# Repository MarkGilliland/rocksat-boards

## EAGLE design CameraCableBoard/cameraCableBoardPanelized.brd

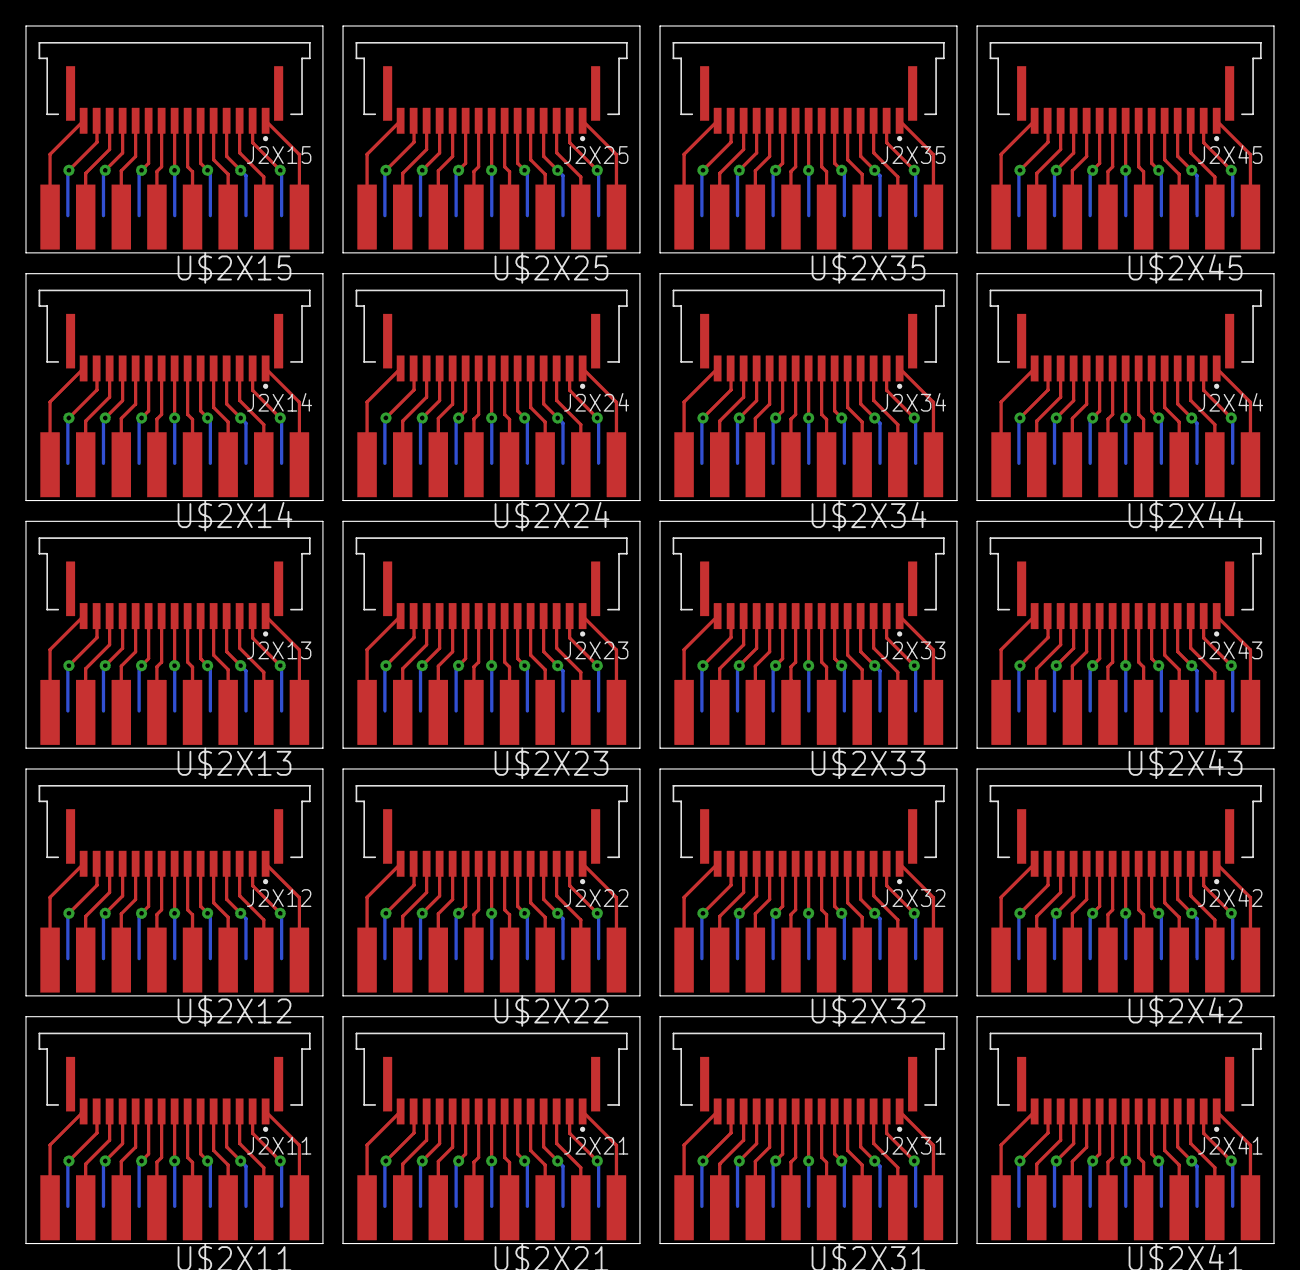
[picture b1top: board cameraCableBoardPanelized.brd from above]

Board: 2 copper layers, 96.0 x 93.7 mm, 40 parts (0 on the bottom side), 300 nets.

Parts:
J2X11, J2X12, J2X13, J2X14, J2X15, J2X21, J2X22, J2X23, J2X24, J2X25, J2X31, J2X32, J2X33, J2X34, J2X35, J2X41, J2X42, J2X43, J2X44, J2X45: AMPHENOL_SFW15R-1STE1LF
U$2X11, U$2X12, U$2X13, U$2X14, U$2X15, U$2X21, U$2X22, U$2X23, U$2X24, U$2X25, U$2X31, U$2X32, U$2X33, U$2X34, U$2X35, U$2X41, U$2X42, U$2X43, U$2X44, U$2X45: DB15-BOARD-EDGE

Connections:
CAM1X11: J2X11.1, U$2X11.P8
CAM1X12: J2X12.1, U$2X12.P8
CAM1X13: J2X13.1, U$2X13.P8
CAM1X14: J2X14.1, U$2X14.P8
CAM1X15: J2X15.1, U$2X15.P8
CAM1X21: J2X21.1, U$2X21.P8
CAM1X22: J2X22.1, U$2X22.P8
CAM1X23: J2X23.1, U$2X23.P8
CAM1X24: J2X24.1, U$2X24.P8
CAM1X25: J2X25.1, U$2X25.P8
CAM1X31: J2X31.1, U$2X31.P8
CAM1X32: J2X32.1, U$2X32.P8
CAM1X33: J2X33.1, U$2X33.P8
CAM1X34: J2X34.1, U$2X34.P8
CAM1X35: J2X35.1, U$2X35.P8
CAM1X41: J2X41.1, U$2X41.P8
CAM1X42: J2X42.1, U$2X42.P8
CAM1X43: J2X43.1, U$2X43.P8
CAM1X44: J2X44.1, U$2X44.P8
CAM1X45: J2X45.1, U$2X45.P8
CAM2X11: J2X11.2, U$2X11.P15
CAM2X12: J2X12.2, U$2X12.P15
CAM2X13: J2X13.2, U$2X13.P15
CAM2X14: J2X14.2, U$2X14.P15
CAM2X15: J2X15.2, U$2X15.P15
CAM2X21: J2X21.2, U$2X21.P15
CAM2X22: J2X22.2, U$2X22.P15
CAM2X23: J2X23.2, U$2X23.P15
CAM2X24: J2X24.2, U$2X24.P15
CAM2X25: J2X25.2, U$2X25.P15
CAM2X31: J2X31.2, U$2X31.P15
CAM2X32: J2X32.2, U$2X32.P15
CAM2X33: J2X33.2, U$2X33.P15
CAM2X34: J2X34.2, U$2X34.P15
CAM2X35: J2X35.2, U$2X35.P15
CAM2X41: J2X41.2, U$2X41.P15
CAM2X42: J2X42.2, U$2X42.P15
CAM2X43: J2X43.2, U$2X43.P15
CAM2X44: J2X44.2, U$2X44.P15
CAM2X45: J2X45.2, U$2X45.P15
CAM3X11: J2X11.3, U$2X11.P7
CAM3X12: J2X12.3, U$2X12.P7
CAM3X13: J2X13.3, U$2X13.P7
CAM3X14: J2X14.3, U$2X14.P7
CAM3X15: J2X15.3, U$2X15.P7
CAM3X21: J2X21.3, U$2X21.P7
CAM3X22: J2X22.3, U$2X22.P7
CAM3X23: J2X23.3, U$2X23.P7
CAM3X24: J2X24.3, U$2X24.P7
CAM3X25: J2X25.3, U$2X25.P7
CAM3X31: J2X31.3, U$2X31.P7
CAM3X32: J2X32.3, U$2X32.P7
CAM3X33: J2X33.3, U$2X33.P7
CAM3X34: J2X34.3, U$2X34.P7
CAM3X35: J2X35.3, U$2X35.P7
CAM3X41: J2X41.3, U$2X41.P7
CAM3X42: J2X42.3, U$2X42.P7
CAM3X43: J2X43.3, U$2X43.P7
CAM3X44: J2X44.3, U$2X44.P7
CAM3X45: J2X45.3, U$2X45.P7
CAM4X11: J2X11.4, U$2X11.P14
CAM4X12: J2X12.4, U$2X12.P14
CAM4X13: J2X13.4, U$2X13.P14
CAM4X14: J2X14.4, U$2X14.P14
CAM4X15: J2X15.4, U$2X15.P14
CAM4X21: J2X21.4, U$2X21.P14
CAM4X22: J2X22.4, U$2X22.P14
CAM4X23: J2X23.4, U$2X23.P14
CAM4X24: J2X24.4, U$2X24.P14
CAM4X25: J2X25.4, U$2X25.P14
CAM4X31: J2X31.4, U$2X31.P14
CAM4X32: J2X32.4, U$2X32.P14
CAM4X33: J2X33.4, U$2X33.P14
CAM4X34: J2X34.4, U$2X34.P14
CAM4X35: J2X35.4, U$2X35.P14
CAM4X41: J2X41.4, U$2X41.P14
CAM4X42: J2X42.4, U$2X42.P14
CAM4X43: J2X43.4, U$2X43.P14
CAM4X44: J2X44.4, U$2X44.P14
CAM4X45: J2X45.4, U$2X45.P14
CAM5X11: J2X11.5, U$2X11.P6
CAM5X12: J2X12.5, U$2X12.P6
CAM5X13: J2X13.5, U$2X13.P6
CAM5X14: J2X14.5, U$2X14.P6
CAM5X15: J2X15.5, U$2X15.P6
CAM5X21: J2X21.5, U$2X21.P6
CAM5X22: J2X22.5, U$2X22.P6
CAM5X23: J2X23.5, U$2X23.P6
CAM5X24: J2X24.5, U$2X24.P6
CAM5X25: J2X25.5, U$2X25.P6
CAM5X31: J2X31.5, U$2X31.P6
CAM5X32: J2X32.5, U$2X32.P6
CAM5X33: J2X33.5, U$2X33.P6
CAM5X34: J2X34.5, U$2X34.P6
CAM5X35: J2X35.5, U$2X35.P6
CAM5X41: J2X41.5, U$2X41.P6
CAM5X42: J2X42.5, U$2X42.P6
CAM5X43: J2X43.5, U$2X43.P6
CAM5X44: J2X44.5, U$2X44.P6
CAM5X45: J2X45.5, U$2X45.P6
CAM6X11: J2X11.6, U$2X11.P13
CAM6X12: J2X12.6, U$2X12.P13
CAM6X13: J2X13.6, U$2X13.P13
CAM6X14: J2X14.6, U$2X14.P13
CAM6X15: J2X15.6, U$2X15.P13
CAM6X21: J2X21.6, U$2X21.P13
CAM6X22: J2X22.6, U$2X22.P13
CAM6X23: J2X23.6, U$2X23.P13
CAM6X24: J2X24.6, U$2X24.P13
CAM6X25: J2X25.6, U$2X25.P13
CAM6X31: J2X31.6, U$2X31.P13
CAM6X32: J2X32.6, U$2X32.P13
CAM6X33: J2X33.6, U$2X33.P13
CAM6X34: J2X34.6, U$2X34.P13
CAM6X35: J2X35.6, U$2X35.P13
CAM6X41: J2X41.6, U$2X41.P13
CAM6X42: J2X42.6, U$2X42.P13
CAM6X43: J2X43.6, U$2X43.P13
CAM6X44: J2X44.6, U$2X44.P13
CAM6X45: J2X45.6, U$2X45.P13
CAM7X11: J2X11.7, U$2X11.P5
CAM7X12: J2X12.7, U$2X12.P5
CAM7X13: J2X13.7, U$2X13.P5
CAM7X14: J2X14.7, U$2X14.P5
CAM7X15: J2X15.7, U$2X15.P5
CAM7X21: J2X21.7, U$2X21.P5
CAM7X22: J2X22.7, U$2X22.P5
CAM7X23: J2X23.7, U$2X23.P5
CAM7X24: J2X24.7, U$2X24.P5
CAM7X25: J2X25.7, U$2X25.P5
CAM7X31: J2X31.7, U$2X31.P5
CAM7X32: J2X32.7, U$2X32.P5
CAM7X33: J2X33.7, U$2X33.P5
CAM7X34: J2X34.7, U$2X34.P5
CAM7X35: J2X35.7, U$2X35.P5
CAM7X41: J2X41.7, U$2X41.P5
CAM7X42: J2X42.7, U$2X42.P5
CAM7X43: J2X43.7, U$2X43.P5
CAM7X44: J2X44.7, U$2X44.P5
CAM7X45: J2X45.7, U$2X45.P5
CAM8X11: J2X11.8, U$2X11.P12
CAM8X12: J2X12.8, U$2X12.P12
CAM8X13: J2X13.8, U$2X13.P12
CAM8X14: J2X14.8, U$2X14.P12
CAM8X15: J2X15.8, U$2X15.P12
CAM8X21: J2X21.8, U$2X21.P12
CAM8X22: J2X22.8, U$2X22.P12
CAM8X23: J2X23.8, U$2X23.P12
CAM8X24: J2X24.8, U$2X24.P12
CAM8X25: J2X25.8, U$2X25.P12
CAM8X31: J2X31.8, U$2X31.P12
CAM8X32: J2X32.8, U$2X32.P12
CAM8X33: J2X33.8, U$2X33.P12
CAM8X34: J2X34.8, U$2X34.P12
CAM8X35: J2X35.8, U$2X35.P12
CAM8X41: J2X41.8, U$2X41.P12
CAM8X42: J2X42.8, U$2X42.P12
CAM8X43: J2X43.8, U$2X43.P12
CAM8X44: J2X44.8, U$2X44.P12
CAM8X45: J2X45.8, U$2X45.P12
CAM9X11: J2X11.9, U$2X11.P4
CAM9X12: J2X12.9, U$2X12.P4
CAM9X13: J2X13.9, U$2X13.P4
CAM9X14: J2X14.9, U$2X14.P4
CAM9X15: J2X15.9, U$2X15.P4
CAM9X21: J2X21.9, U$2X21.P4
CAM9X22: J2X22.9, U$2X22.P4
CAM9X23: J2X23.9, U$2X23.P4
CAM9X24: J2X24.9, U$2X24.P4
CAM9X25: J2X25.9, U$2X25.P4
CAM9X31: J2X31.9, U$2X31.P4
CAM9X32: J2X32.9, U$2X32.P4
CAM9X33: J2X33.9, U$2X33.P4
CAM9X34: J2X34.9, U$2X34.P4
CAM9X35: J2X35.9, U$2X35.P4
CAM9X41: J2X41.9, U$2X41.P4
CAM9X42: J2X42.9, U$2X42.P4
CAM9X43: J2X43.9, U$2X43.P4
CAM9X44: J2X44.9, U$2X44.P4
CAM9X45: J2X45.9, U$2X45.P4
CAM10X11: J2X11.10, U$2X11.P11
CAM10X12: J2X12.10, U$2X12.P11
CAM10X13: J2X13.10, U$2X13.P11
CAM10X14: J2X14.10, U$2X14.P11
CAM10X15: J2X15.10, U$2X15.P11
CAM10X21: J2X21.10, U$2X21.P11
CAM10X22: J2X22.10, U$2X22.P11
CAM10X23: J2X23.10, U$2X23.P11
CAM10X24: J2X24.10, U$2X24.P11
CAM10X25: J2X25.10, U$2X25.P11
CAM10X31: J2X31.10, U$2X31.P11
CAM10X32: J2X32.10, U$2X32.P11
CAM10X33: J2X33.10, U$2X33.P11
CAM10X34: J2X34.10, U$2X34.P11
CAM10X35: J2X35.10, U$2X35.P11
CAM10X41: J2X41.10, U$2X41.P11
CAM10X42: J2X42.10, U$2X42.P11
CAM10X43: J2X43.10, U$2X43.P11
CAM10X44: J2X44.10, U$2X44.P11
CAM10X45: J2X45.10, U$2X45.P11
CAM11X11: J2X11.11, U$2X11.P3
CAM11X12: J2X12.11, U$2X12.P3
CAM11X13: J2X13.11, U$2X13.P3
CAM11X14: J2X14.11, U$2X14.P3
CAM11X15: J2X15.11, U$2X15.P3
CAM11X21: J2X21.11, U$2X21.P3
CAM11X22: J2X22.11, U$2X22.P3
CAM11X23: J2X23.11, U$2X23.P3
CAM11X24: J2X24.11, U$2X24.P3
CAM11X25: J2X25.11, U$2X25.P3
CAM11X31: J2X31.11, U$2X31.P3
CAM11X32: J2X32.11, U$2X32.P3
CAM11X33: J2X33.11, U$2X33.P3
CAM11X34: J2X34.11, U$2X34.P3
CAM11X35: J2X35.11, U$2X35.P3
CAM11X41: J2X41.11, U$2X41.P3
CAM11X42: J2X42.11, U$2X42.P3
CAM11X43: J2X43.11, U$2X43.P3
CAM11X44: J2X44.11, U$2X44.P3
CAM11X45: J2X45.11, U$2X45.P3
CAM12X11: J2X11.12, U$2X11.P10
CAM12X12: J2X12.12, U$2X12.P10
CAM12X13: J2X13.12, U$2X13.P10
CAM12X14: J2X14.12, U$2X14.P10
CAM12X15: J2X15.12, U$2X15.P10
CAM12X21: J2X21.12, U$2X21.P10
CAM12X22: J2X22.12, U$2X22.P10
CAM12X23: J2X23.12, U$2X23.P10
CAM12X24: J2X24.12, U$2X24.P10
CAM12X25: J2X25.12, U$2X25.P10
CAM12X31: J2X31.12, U$2X31.P10
CAM12X32: J2X32.12, U$2X32.P10
CAM12X33: J2X33.12, U$2X33.P10
CAM12X34: J2X34.12, U$2X34.P10
CAM12X35: J2X35.12, U$2X35.P10
CAM12X41: J2X41.12, U$2X41.P10
CAM12X42: J2X42.12, U$2X42.P10
CAM12X43: J2X43.12, U$2X43.P10
CAM12X44: J2X44.12, U$2X44.P10
CAM12X45: J2X45.12, U$2X45.P10
CAM13X11: J2X11.13, U$2X11.P2
CAM13X12: J2X12.13, U$2X12.P2
CAM13X13: J2X13.13, U$2X13.P2
CAM13X14: J2X14.13, U$2X14.P2
CAM13X15: J2X15.13, U$2X15.P2
CAM13X21: J2X21.13, U$2X21.P2
CAM13X22: J2X22.13, U$2X22.P2
CAM13X23: J2X23.13, U$2X23.P2
CAM13X24: J2X24.13, U$2X24.P2
CAM13X25: J2X25.13, U$2X25.P2
CAM13X31: J2X31.13, U$2X31.P2
CAM13X32: J2X32.13, U$2X32.P2
CAM13X33: J2X33.13, U$2X33.P2
CAM13X34: J2X34.13, U$2X34.P2
CAM13X35: J2X35.13, U$2X35.P2
CAM13X41: J2X41.13, U$2X41.P2
CAM13X42: J2X42.13, U$2X42.P2
CAM13X43: J2X43.13, U$2X43.P2
CAM13X44: J2X44.13, U$2X44.P2
CAM13X45: J2X45.13, U$2X45.P2
CAM14X11: J2X11.14, U$2X11.P9
CAM14X12: J2X12.14, U$2X12.P9
CAM14X13: J2X13.14, U$2X13.P9
CAM14X14: J2X14.14, U$2X14.P9
CAM14X15: J2X15.14, U$2X15.P9
CAM14X21: J2X21.14, U$2X21.P9
CAM14X22: J2X22.14, U$2X22.P9
CAM14X23: J2X23.14, U$2X23.P9
CAM14X24: J2X24.14, U$2X24.P9
CAM14X25: J2X25.14, U$2X25.P9
CAM14X31: J2X31.14, U$2X31.P9
CAM14X32: J2X32.14, U$2X32.P9
CAM14X33: J2X33.14, U$2X33.P9
CAM14X34: J2X34.14, U$2X34.P9
CAM14X35: J2X35.14, U$2X35.P9
CAM14X41: J2X41.14, U$2X41.P9
CAM14X42: J2X42.14, U$2X42.P9
CAM14X43: J2X43.14, U$2X43.P9
CAM14X44: J2X44.14, U$2X44.P9
CAM14X45: J2X45.14, U$2X45.P9
CAM15X11: J2X11.15, U$2X11.P1
CAM15X12: J2X12.15, U$2X12.P1
CAM15X13: J2X13.15, U$2X13.P1
CAM15X14: J2X14.15, U$2X14.P1
CAM15X15: J2X15.15, U$2X15.P1
CAM15X21: J2X21.15, U$2X21.P1
CAM15X22: J2X22.15, U$2X22.P1
CAM15X23: J2X23.15, U$2X23.P1
CAM15X24: J2X24.15, U$2X24.P1
CAM15X25: J2X25.15, U$2X25.P1
CAM15X31: J2X31.15, U$2X31.P1
CAM15X32: J2X32.15, U$2X32.P1
CAM15X33: J2X33.15, U$2X33.P1
CAM15X34: J2X34.15, U$2X34.P1
CAM15X35: J2X35.15, U$2X35.P1
CAM15X41: J2X41.15, U$2X41.P1
CAM15X42: J2X42.15, U$2X42.P1
CAM15X43: J2X43.15, U$2X43.P1
CAM15X44: J2X44.15, U$2X44.P1
CAM15X45: J2X45.15, U$2X45.P1

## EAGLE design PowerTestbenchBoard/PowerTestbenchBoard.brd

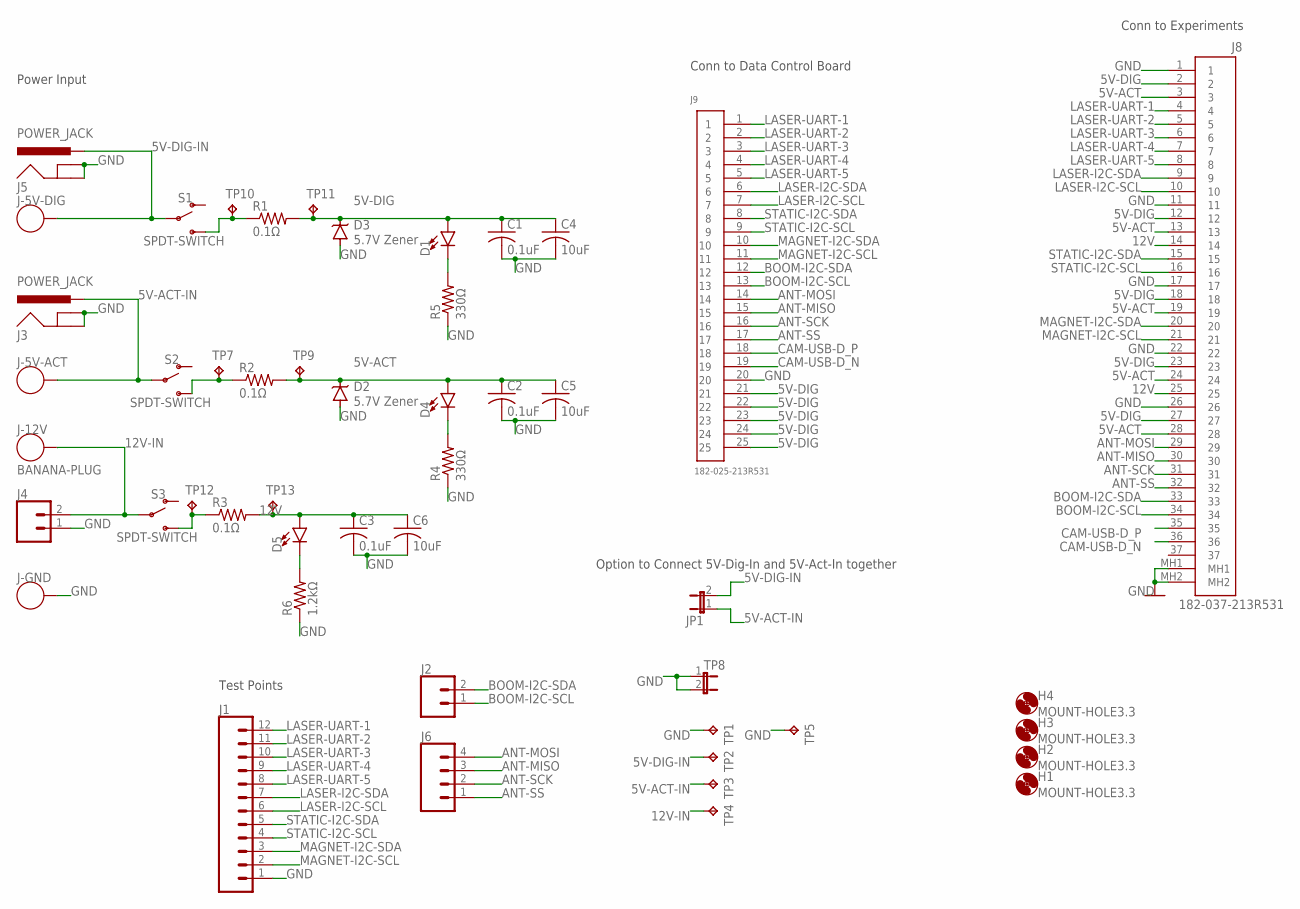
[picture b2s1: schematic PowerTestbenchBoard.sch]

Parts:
C1, C2, C3: 0.1uF; C0805
C4, C5, C6: 10uF; C0805
D1, D4, D5: LED-3MM-NO_SILK; LED_3MM-NS
D2, D3: 5.7V Zener; SMB
H1, H2, H3, H4: MOUNT-HOLE3.3; 3,3
J1: CONN_12; 1X12
J2: CONN_02; 1X02
J3, J5: POWER_JACK; POWER_JACK_PTH
J4: CONN_023.5MM; SCREWTERMINAL-3.5MM-2
J6: CONN_04; 1X04
J8: 182-037-213R531
J9: 182-025-213R531
J-5V-ACT, J-5V-DIG, J-12V: BANANA-PLUG; BANANA-JACK
J-GND: BANANA-PLUG; BANANA-JACK
JP1: JP1E; JP1
R1, R2, R3: 0.1Ω; R1206
R4, R5: 330Ω; R0805
R6: 1.2kΩ; R0805
S1, S2, S3: SPDT-SWITCH; SWITCH_SPDT_PTH_11.6X4.0MM
TP1, TP2, TP3, TP4, TP5, TP7, TP9, TP10, TP11, TP12, TP13: TPPAD1-13; P1-13
TP8: JP1E; JP1

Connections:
5V-ACT: C2.1, C5.1, D2.C, D4.A, J8.3, J8.13, J8.19, J8.24, J8.28, R2.2, TP9.TP
5V-ACT-IN: J3.PWR, J-5V-ACT.P$1, J-5V-ACT.P$2, JP1.1, S2.2, TP3.TP
5V-DIG: C1.1, C4.1, D1.A, D3.C, J8.2, J8.12, J8.18, J8.23, J8.27, J9.21, J9.22, J9.23, J9.24, J9.25, R1.2, TP11.TP
5V-DIG-IN: J5.PWR, J-5V-DIG.P$1, J-5V-DIG.P$2, JP1.2, S1.2, TP2.TP
12V: C3.1, C6.1, D5.A, J8.14, J8.25, R3.2, TP13.TP
12V-IN: J4.2, J-12V.P$1, J-12V.P$2, S3.2, TP4.TP
ANT-MISO: J6.3, J8.30, J9.15
ANT-MOSI: J6.4, J8.29, J9.14
ANT-SCK: J6.2, J8.31, J9.16
ANT-SS: J6.1, J8.32, J9.17
BOOM-I2C-SCL: J2.1, J8.34, J9.13
BOOM-I2C-SDA: J2.2, J8.33, J9.12
CAM-USB-D_N: J8.36, J9.19
CAM-USB-D_P: J8.35, J9.18
GND: C1.2, C2.2, C3.2, C4.2, C5.2, C6.2, D2.A, D3.A, J1.1, J3.GND, J3.GNDBREAK, J4.1, J5.GND, J5.GNDBREAK, J8.1, J8.11, J8.17, J8.22, J8.26, J8.MH1, J8.MH2, J9.20, J-GND.P$1, J-GND.P$2, R4.1, R5.1, R6.1, TP1.TP, TP5.TP, TP8.1, TP8.2
LASER-I2C-SCL: J1.6, J8.10, J9.7
LASER-I2C-SDA: J1.7, J8.9, J9.6
LASER-UART-1: J1.12, J8.4, J9.1
LASER-UART-2: J1.11, J8.5, J9.2
LASER-UART-3: J1.10, J8.6, J9.3
LASER-UART-4: J1.9, J8.7, J9.4
LASER-UART-5: J1.8, J8.8, J9.5
MAGNET-I2C-SCL: J1.2, J8.21, J9.11
MAGNET-I2C-SDA: J1.3, J8.20, J9.10
unnamed: R1.1, S1.1 (S), TP10.TP
unnamed: R2.1, S2.1 (S), TP7.TP
unnamed: R3.1, S3.1 (S), TP12.TP
unnamed: D4.K (C), R4.2
unnamed: D5.K (C), R6.2
unnamed: D1.K (C), R5.2
STATIC-I2C-SCL: J1.4, J8.16, J9.9
STATIC-I2C-SDA: J1.5, J8.15, J9.8

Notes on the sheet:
Test Points
Power Input
Conn to Data Control Board
Conn to Experiments
Option to Connect 5V-Dig-In and 5V-Act-In together

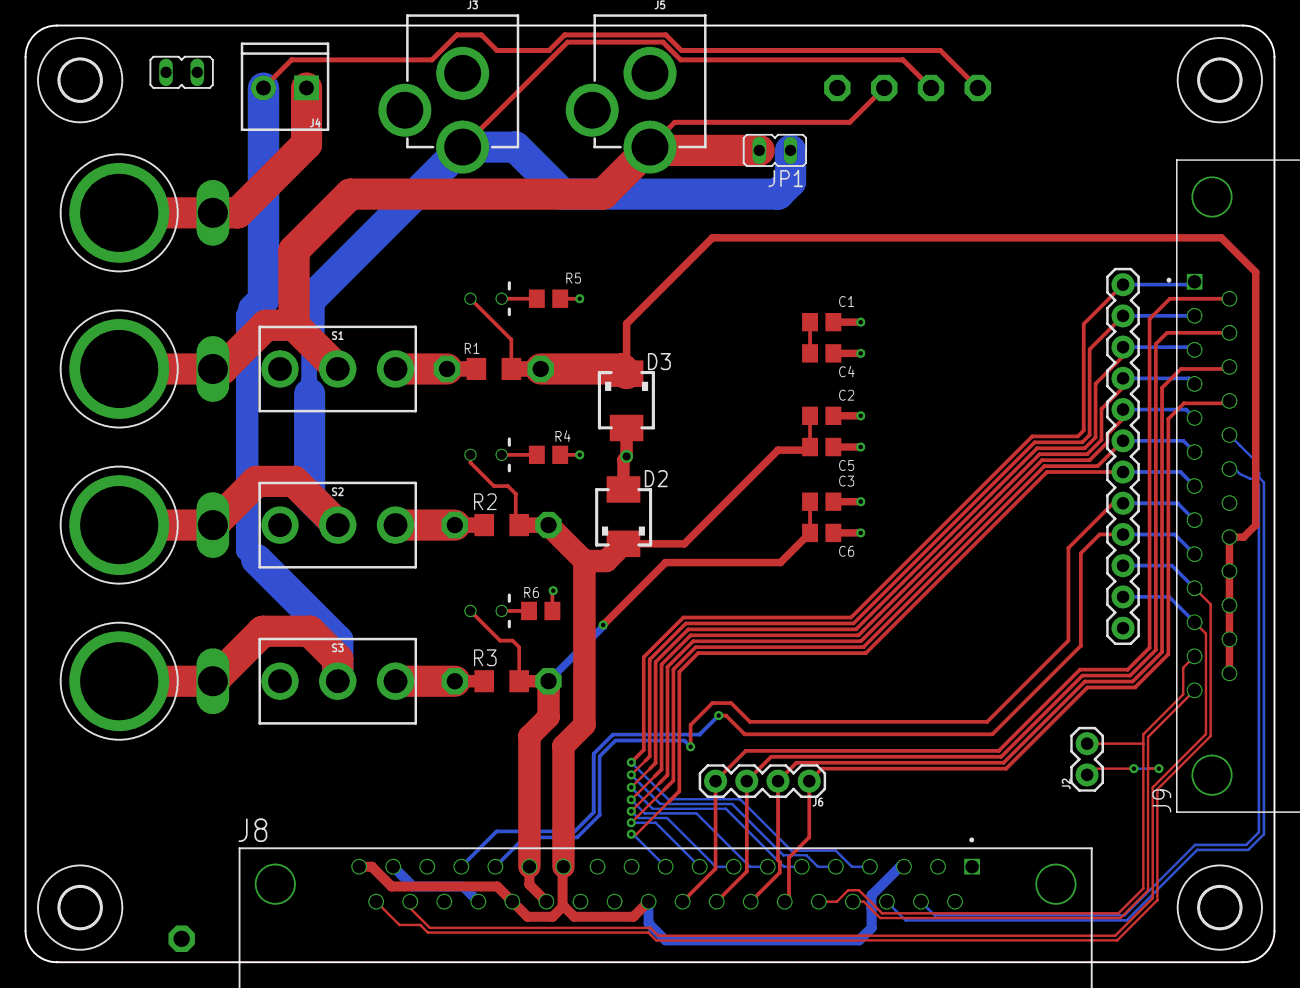
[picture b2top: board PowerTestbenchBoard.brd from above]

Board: 2 copper layers, 101.6 x 76.2 mm, 49 parts (0 on the bottom side), 32 nets.

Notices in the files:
parts and their libraries:
SparkFun-Connectors: Licensing: Creative Commons ShareAlike 4.0 International - https://creativecommons.org/licenses/by-sa/4.0
